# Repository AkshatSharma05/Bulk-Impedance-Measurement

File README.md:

# Bulk Impedance Measurement Tool
## Overview

This repository contains the PCB design for a bulk impedance measurement tool built around an ESP32, an AD9833 DDS signal generator, and the internal ADC for measurement.

The system generates a sinusoidal excitation signal, conditions and buffers it, and applies it to a voltage divider formed by a known resistor (R_known) and an external unknown impedance (Z_unknown). The ESP32 measures the input and output voltages using its ADC and computes the unknown impedance using:

```Z_unknown = R_known × (Vout / (Vin − Vout))```

## Notes
- The design is intended for low-voltage impedance measurement experiments and prototyping.
- Best sensitivity is achieved when R_known ≈ Z_unknown.
- All measurements are performed using AC excitation.
- The DIP Switches provided can be used to change the value of R_known -> 1K, 10K, 100K.

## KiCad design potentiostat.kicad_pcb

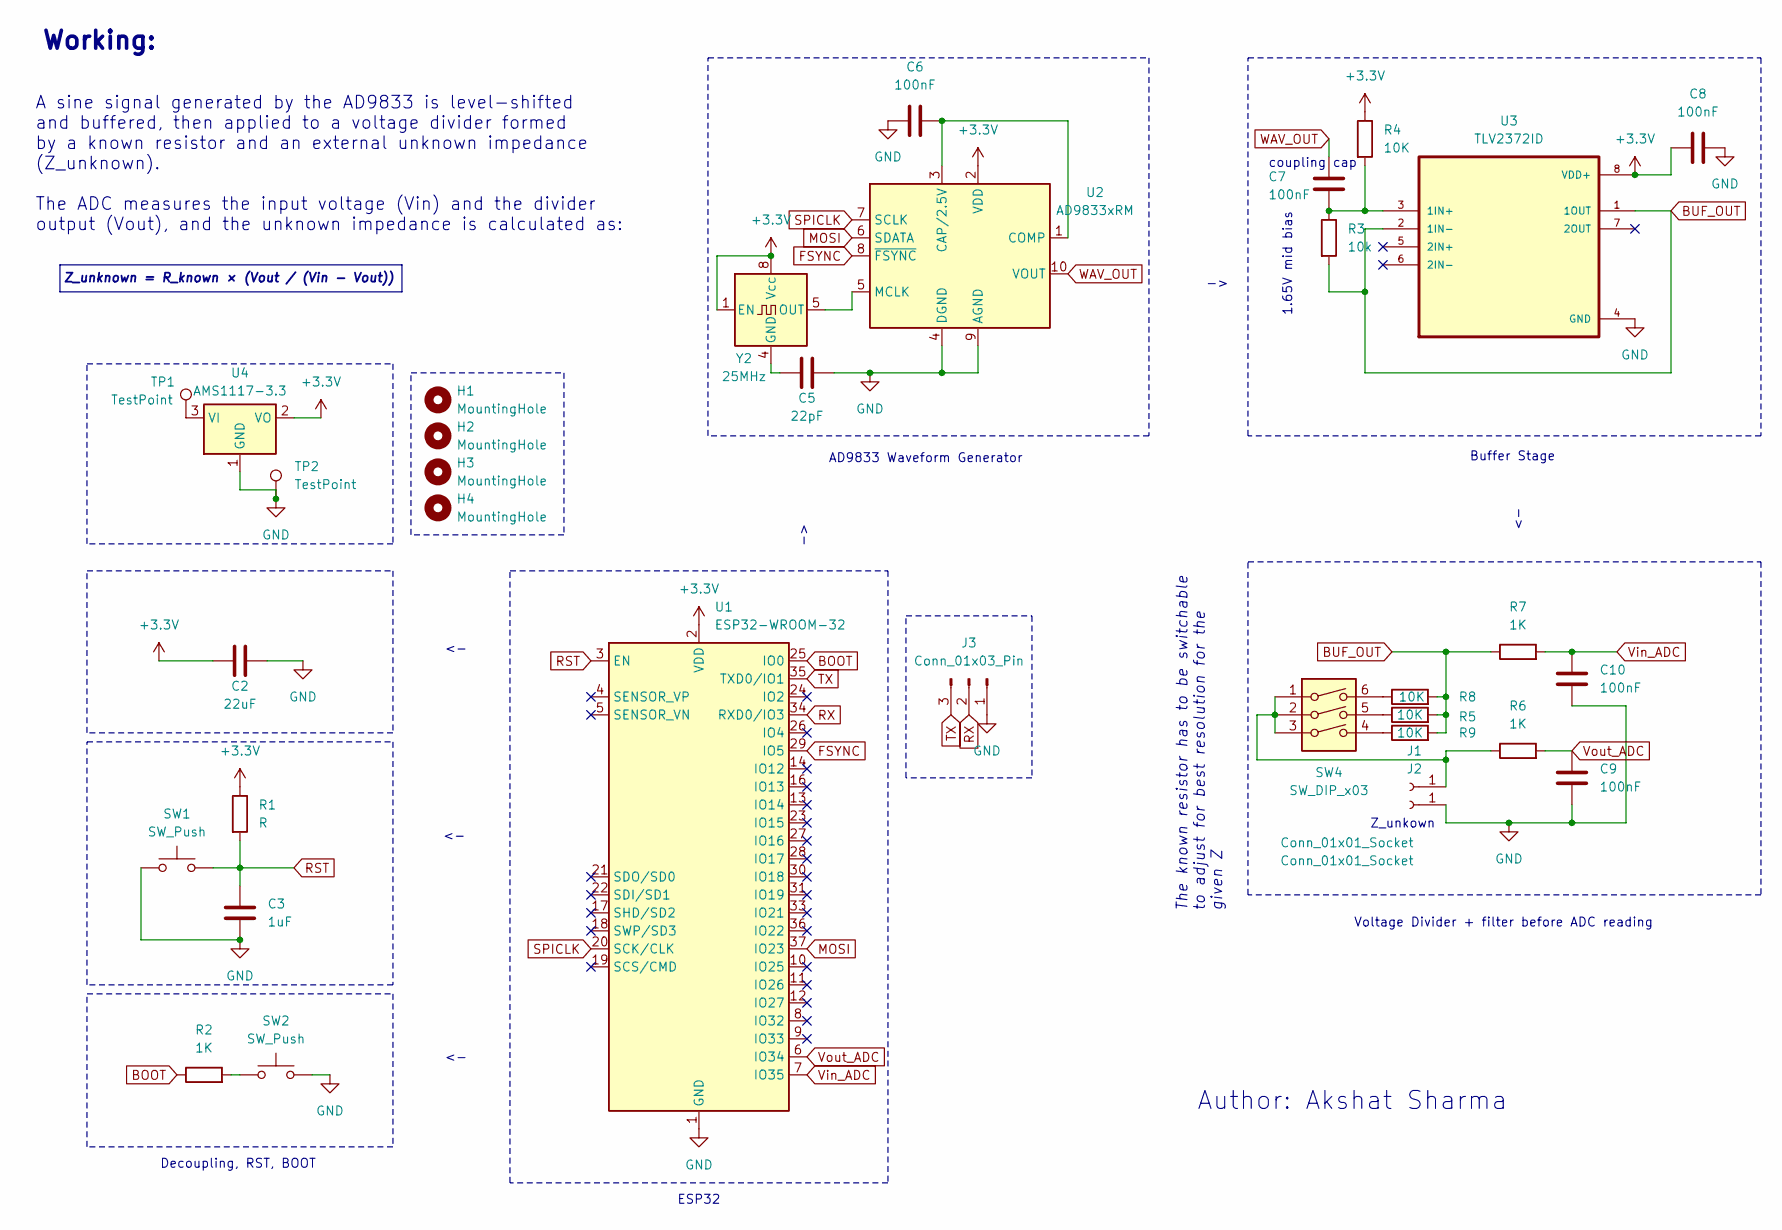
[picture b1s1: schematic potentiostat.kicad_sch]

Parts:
C2: 22uF; C_0201_0603Metric
C3: 1uF; C_0201_0603Metric
C5: 22pF; C_0201_0603Metric
C6, C7, C8, C9, C10: 100nF; C_0201_0603Metric
H1, H2, H3, H4: MountingHole; MountingHole_2.5mm
J1, J2: Conn_01x01_Socket; BNC_TEConnectivity_1478204_Vertical
J3: Conn_01x03_Pin; PinHeader_1x03_P2.54mm_Horizontal
R1: R; R_0603_1608Metric
R2, R6, R7: 1K; R_0603_1608Metric
R3: 10k; R_0603_1608Metric
R4, R5, R8, R9: 10K; R_0603_1608Metric
SW1, SW2: SW_Push; SW_Tactile_SPST_NO_Straight_CK_PTS636Sx25SMTRLFS
SW4: SW_DIP_x03; SW_DIP_SPSTx03_Slide_KingTek_DSHP03TJ_W5.25mm_P1.27mm_JPin
TP1, TP2: TestPoint; TestPoint_Pad_2.5x2.5mm
U1: ESP32-WROOM-32
U2: AD9833xRM; MSOP-10_3x3mm_P0.5mm
U3: TLV2372ID; SOIC127P599X175-8N; DigiKey_Part_Number TLV2372ID-ND
U4: AMS1117-3.3; SOT-223-3_TabPin2
Y2: 25MHz; Oscillator_DIP-8

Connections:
+3.3V: C2.1, C8.1, R1.1, R4.1, U1.2 (VDD), U2.2 (VDD), U3.8 (VDD+), U4.2 (VO), Y2.1 (EN), Y2.8 (Vcc)
BOOT: R2.1, U1.25 (IO0)
BUF_OUT: R3.2, R5.2, R7.1, R8.2, R9.2, U3.1 (1OUT), U3.2 (1IN-)
FSYNC: U1.29 (IO5), U2.8 (~FSYNC)
GND: C2.2, C3.2, C5.2, C6.1, C8.2, C9.1, C10.2, J2.1, J3.1, SW1.1, SW2.2, TP2.1, U1.1 (GND), U1.15 (GND), U1.38 (GND), U1.39 (GND), U2.4 (DGND), U2.9 (AGND), U3.4 (GND), U4.1 (GND); also elsewhere on the board
MOSI: U1.37 (IO23), U2.6 (SDATA)
unnamed: J1.1, R6.1, SW4.1, SW4.2, SW4.3
unnamed: R2.2, SW2.1
unnamed: R5.1, SW4.5
unnamed: R8.1, SW4.6
unnamed: R9.1, SW4.4
unnamed: C6.2, U2.1 (COMP), U2.3 (CAP/2.5V)
unnamed: U2.5 (MCLK), Y2.5 (OUT)
unnamed: C7.2, R3.1, R4.2, U3.3 (1IN+)
unnamed 14: TP1.1, U4.3 (VI); also elsewhere on the board
unnamed: C5.1, Y2.4 (GND)
RST: C3.1, R1.2, SW1.2, U1.3 (EN)
RX: J3.2, U1.34 (RXD0/IO3)
SPICLK: U1.20 (SCK/CLK), U2.7 (SCLK)
TX: J3.3, U1.35 (TXD0/IO1)
Vin_ADC: C10.1, R7.2, U1.7 (IO35)
Vout_ADC: C9.2, R6.2, U1.6 (IO34)
WAV_OUT: C7.1, U2.10 (VOUT)

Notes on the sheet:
1.65V mid bias
coupling cap
Voltage Divider + filter before ADC reading
Z_unkown
AD9833 Waveform Generator
Z_unknown = R_known × (Vout / (Vin − Vout))
Author: Akshat Sharma
ESP32
The known resistor has to be switchable to adjust for best resolution for the given Z
Decoupling, RST, BOOT
Working:
Buffer Stage
A sine signal generated by the AD9833 is level-shifted and buffered, then applied to a voltage divider formed by a known resistor and an external unknown impedance (Z_unknown). The ADC measures the input voltage (Vin) and the divider output (Vout), and the unknown impedance is calculated as:

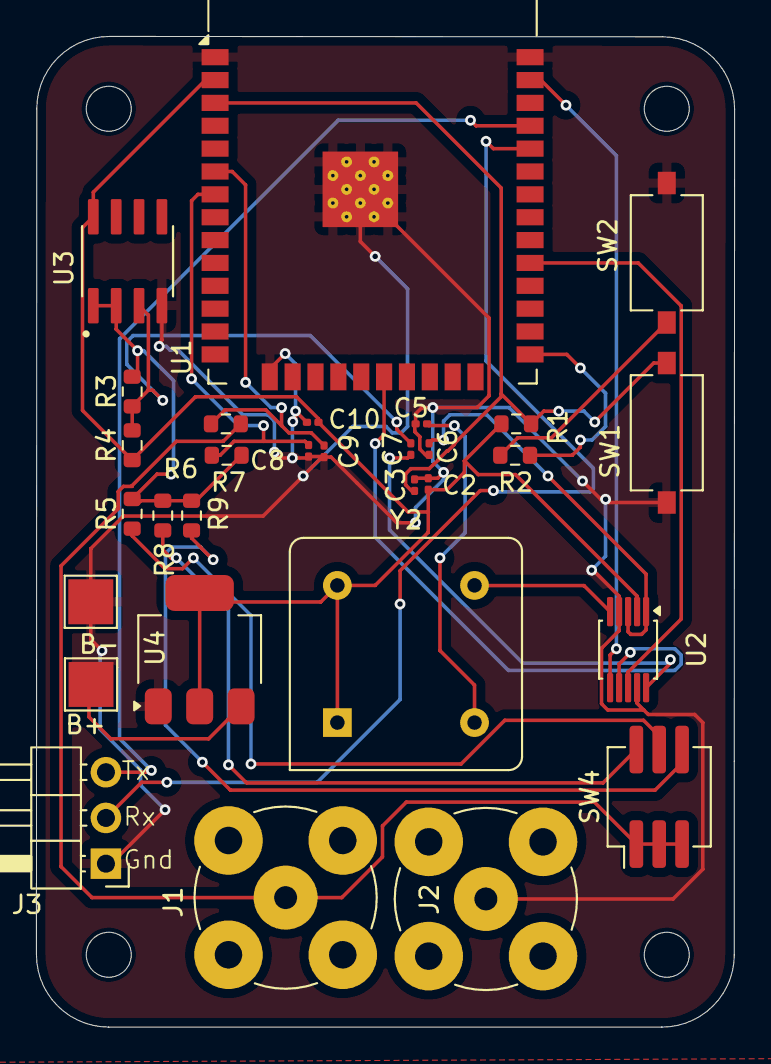
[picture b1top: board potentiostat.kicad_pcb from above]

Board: 2 copper layers, 38.8 x 55.0 mm, 34 parts (0 on the bottom side), 23 nets.

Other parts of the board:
B+: TestPoint; TestPoint_Pad_2.5x2.5mm
B-: TestPoint; TestPoint_Pad_2.5x2.5mm

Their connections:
GND: B-.1; also elsewhere on the board
unnamed 14: B+.1; also elsewhere on the board

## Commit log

2026-05-08 completed pcb
2026-05-08 dip switch added
2026-05-08 debugging pins
2026-05-08 schm pdf
2026-05-08 Add README
    Added detailed overview and notes for the bulk impedance measurement tool.
